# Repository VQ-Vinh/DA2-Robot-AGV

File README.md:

<div align="center">

# 🤖 DA2 · Robot AGV kho hàng kiểu Kiva

**Xe tự hành chui gầm, nâng kệ hàng, chở tới trạm lấy hàng rồi trả về ô và tự đi sạc.**

ROS 2 Jazzy · Nav2 · Gazebo Harmonic · Raspberry Pi 5 · STM32F4 · FreeRTOS · KiCad · FreeCAD

[Mô phỏng & ROS 2](RasPi/README.md) · [Nhật ký quá trình](REPORT.md) · [Firmware STM32](STM32/) · [Mô hình cơ khí](CAD/README.md) · [Mạch PCB](PCB/)

</div>

---

## ✨ Xe làm được gì

| 📦 Nhận đơn | 🛞 Chui gầm & nâng kệ | 🚚 Chở tới trạm | 🔋 Tự sạc | 🚨 Xử lý sự cố |
|:---:|:---:|:---:|:---:|:---:|
| Hàng đợi, ưu tiên, huỷ đơn trên web | Lidar tìm 4 chân kệ, căn giữa ≤ 1 cm | Nav2 + vùng cấm, footprint đổi theo tải | Pin thấp thì về trạm, sạc đủ mới nhận đơn | Dừng khẩn, đường bị chặn, rơi kệ |

---

## 🗺️ Kho hàng

```mermaid
flowchart LR
    subgraph W["Tây kho"]
        IN(["🔵 Khu nhập hàng"])
        CH(["🟢 Trạm sạc"])
        PK(["🟠 Trạm lấy hàng"])
    end
    subgraph N["Dãy bắc · xe vào hướng +y"]
        N1[N1] --- N2[N2] --- N3[N3] --- N4[N4] --- N5[N5]
    end
    AISLE{{"Lối giữa rộng 2.45 m"}}
    subgraph S["Dãy nam · xe vào hướng −y"]
        S1[S1] --- S2[S2] --- S3[S3] --- S4[S4] --- S5[S5]
    end
    W <--> AISLE
    AISLE <--> N
    AISLE <--> S
```

8 kệ 0.75 × 0.75 m nằm trong 10 ô, cách nhau 1.1 m. Bố trí lấy từ một file duy nhất, [`shelves.yaml`](RasPi/src/agv_mission/config/shelves.yaml), từ đó sinh ra world Gazebo, danh sách dock của Nav2 và mặt nạ vùng cấm.

---

## 🧩 Kiến trúc

```mermaid
flowchart TB
    subgraph USER["👤 Người vận hành"]
        WEB["🌐 Web dashboard<br/>điện thoại / laptop"]
    end

    subgraph PI["🍓 Raspberry Pi 5 · ROS 2 Jazzy"]
        DASH["web_dashboard<br/>REST + SSE"]
        OM["order_manager<br/>hàng đợi · SQLite · sự cố"]
        NAV["Nav2<br/>planner · RPP · docking · behaviors"]
        LOC["AMCL + EKF<br/>imu_bias"]
        PM["payload_manager<br/>lọc scan · footprint"]
        SD["shelf_detector<br/>tìm 4 chân kệ"]
    end

    subgraph MCU["⚙️ STM32F407 · FreeRTOS"]
        SPD["PID tốc độ + feedforward"]
        ENC["Encoder"]
        DRV["TB6612FNG × 2"]
        LIFTD["A4988<br/>cơ cấu nâng"]
    end

    LIDAR(["📡 YDLidar"])
    IMU(["🧭 BNO055"])
    BAT(["🔋 INA219"])
    MOT(["4 × GA25-370"])

    WEB <-->|HTTP| DASH
    DASH <--> OM
    OM -->|goal, dock| NAV
    NAV -->|cmd_vel| MCU
    LIDAR --> PM --> NAV
    LIDAR --> SD --> NAV
    LOC --> NAV
    MCU -->|odom, IMU, pin| LOC
    IMU --> MCU
    BAT --> MCU
    SPD --> DRV --> MOT
    LIFTD --> LIFT(["⏫ Động cơ bước nâng kệ"])
    MOT --> ENC --> SPD
```

---

## 🔁 Một đơn hàng

```mermaid
sequenceDiagram
    autonumber
    actor U as 👤 Người vận hành
    participant OM as order_manager
    participant N as Nav2 / docking
    participant L as Cơ cấu nâng

    U->>OM: add ke_03 tram_lay_hang
    OM->>N: tới staging trước ô (đoạn cuối thẳng)
    OM->>N: chui gầm theo chân kệ (lidar)
    OM->>OM: kiểm tra hướng ≤ 8°
    OM->>L: nâng
    OM->>N: lùi ra · chở tới trạm
    OM-->>U: đã tới, chờ lấy hàng
    U->>OM: confirm
    OM->>N: về ô · vào ô theo bản đồ
    OM->>OM: kiểm tra hướng ≤ 8°, vị trí ≤ 10 cm
    OM->>L: hạ
    OM->>N: lùi ra · về trạm sạc
```

---

## 🚨 Khi có sự cố

```mermaid
flowchart LR
    E{"Sự cố"} -->|Dừng khẩn<br/>Đường bị chặn > 60 s| R["⏸️ Xe dừng<br/>chờ người"]
    E -->|Rơi kệ<br/>Cơ cấu nâng lỗi| F["⛔ Đơn lỗi<br/>kệ chưa rõ vị trí"]
    E -->|Lỗi trước khi nâng kệ| Q["↩️ Trả đơn về hàng đợi"]
    R -->|"Đã xử lý"| C["▶️ Làm lại đúng bước đang dở"]
    F -->|"shelf ke_xx Ny"| C2["📍 Cập nhật vị trí kệ"]
```

```mermaid
flowchart LR
    B["🔋 Pin < 30 % + 10 % dự trữ cho đơn"] --> G["Về trạm sạc"] --> H["Sạc tới 80 %"] --> J["Nhận đơn tiếp"]
```

---

## 🧭 Định vị

```mermaid
flowchart LR
    ENC["Encoder bánh"] --> WO["/wheel/odom<br/>vx tin được · wz kém"]
    GYRO["Gyro"] --> RAW["/imu/raw"] --> IB["imu_bias<br/>học bias khi bánh đứng yên"] --> IMU["/imu"]
    WO --> EKF["EKF"]
    IMU --> EKF
    EKF --> ODOM["/odom"]
    ODOM --> AMCL["AMCL + bản đồ"]
    SCAN["Lidar"] --> AMCL
    AMCL --> MAP["vị trí trên bản đồ"]
```

---

## 📊 Kết quả trong mô phỏng

8 đơn liên tiếp, có mô phỏng vùng chết động cơ giống firmware (≥ 100 RPM):

| | Trước khi chỉnh | Sau khi chỉnh |
|---|:---:|:---:|
| Đơn xong | 8/8 | **8/8** |
| Thời gian TB / đơn | 105 s | **88 s** |
| Quay thừa khi trả kệ (lớn nhất) | 4198° | **75°** |
| Nav2 phải tự hồi phục | nhiều lần | **0** |
| Góc trôi khi đứng yên 5 phút | 2.4°–12° | **0.05°** |

| Bài thử | Kết quả |
|---|---|
| Chui gầm theo chân kệ (kệ đặt lệch) | 6/6, lệch ngang ≤ 0.9 cm · theo bản đồ chỉ 2/6 |
| Đơn hàng + ưu tiên + huỷ | 3/3 |
| Sạc giữa chừng | 3/3 đơn, tự về sạc rồi làm tiếp |
| Sự cố (dừng khẩn, rơi kệ, tường chắn) | dừng khẩn & rơi kệ: 4/4 lần · tường chắn: 2/4 lần |

Cách đo, các lần sai và cách sửa: [REPORT.md](REPORT.md).

---

## 🛣️ Tiến độ

```mermaid
timeline
    title Các mốc chính
    09/2026 : Firmware STM32 · PID tốc độ
            : Chọn ROS 2 Jazzy + Gazebo Harmonic
    10/2026 : Mô phỏng · EKF · SLAM · Nav2
            : Web dashboard
            : Kiva 1 · nâng kệ · Kiva 2 · tìm chân kệ
            : Kiva 3 · đơn hàng · Kiva 4 · pin & sạc · Kiva 5 · sự cố
            : Mô hình cơ khí FreeCAD
            : PCB · chốt linh kiện · sơ đồ chân CubeMX · sơ đồ nguyên lý · xếp linh kiện nháp
            : PCB 2 lớp · đi dây · DRC sạch · Gerber JLCPCB
            : CAD · PCB thật · công tắc hành trình
    Tiếp theo : Đặt mạch · ướm footprint với module thật · mua linh kiện
              : Firmware 4 bánh + cơ cấu nâng · cầu nối UART Pi ↔ STM32
              : Lắp và chạy trên xe thật
```

---

## 🚀 Chạy thử

```bash
# WSL Ubuntu 24.04 + ROS 2 Jazzy (xem RasPi/README.md để cài)
cd ~/agv_ws && colcon build --symlink-install && source install/setup.bash
ros2 launch agv_gazebo sim.launch.py nav:=true
```

Sau đó mở **http://localhost:8080**, chọn kệ và trạm rồi bấm **Tạo đơn**.

---

## 📁 Cấu trúc repo

```mermaid
flowchart LR
    R["📂 Src"] --> RP["📂 RasPi/src<br/>ROS 2"]
    R --> ST["📂 STM32<br/>firmware"]
    R --> RE["📄 REPORT.md<br/>nhật ký"]
    R --> CA["📂 CAD<br/>mô hình FreeCAD"]
    R --> PC["📂 PCB<br/>board mẹ KiCad"]
    RP --> D["agv_description<br/>URDF"]
    RP --> G["agv_gazebo<br/>world · sim · bài thử"]
    RP --> L["agv_localization<br/>EKF · imu_bias"]
    RP --> NV["agv_navigation<br/>SLAM · Nav2 · docking"]
    RP --> M["agv_mission<br/>đơn hàng · dashboard"]
    ST --> APP["App<br/>logic"]
    ST --> MOD["Modules<br/>driver"]
    ST --> CORE["Core<br/>CubeMX sinh"]
```

<div align="center">

Đồ án 2 · HK261

</div>

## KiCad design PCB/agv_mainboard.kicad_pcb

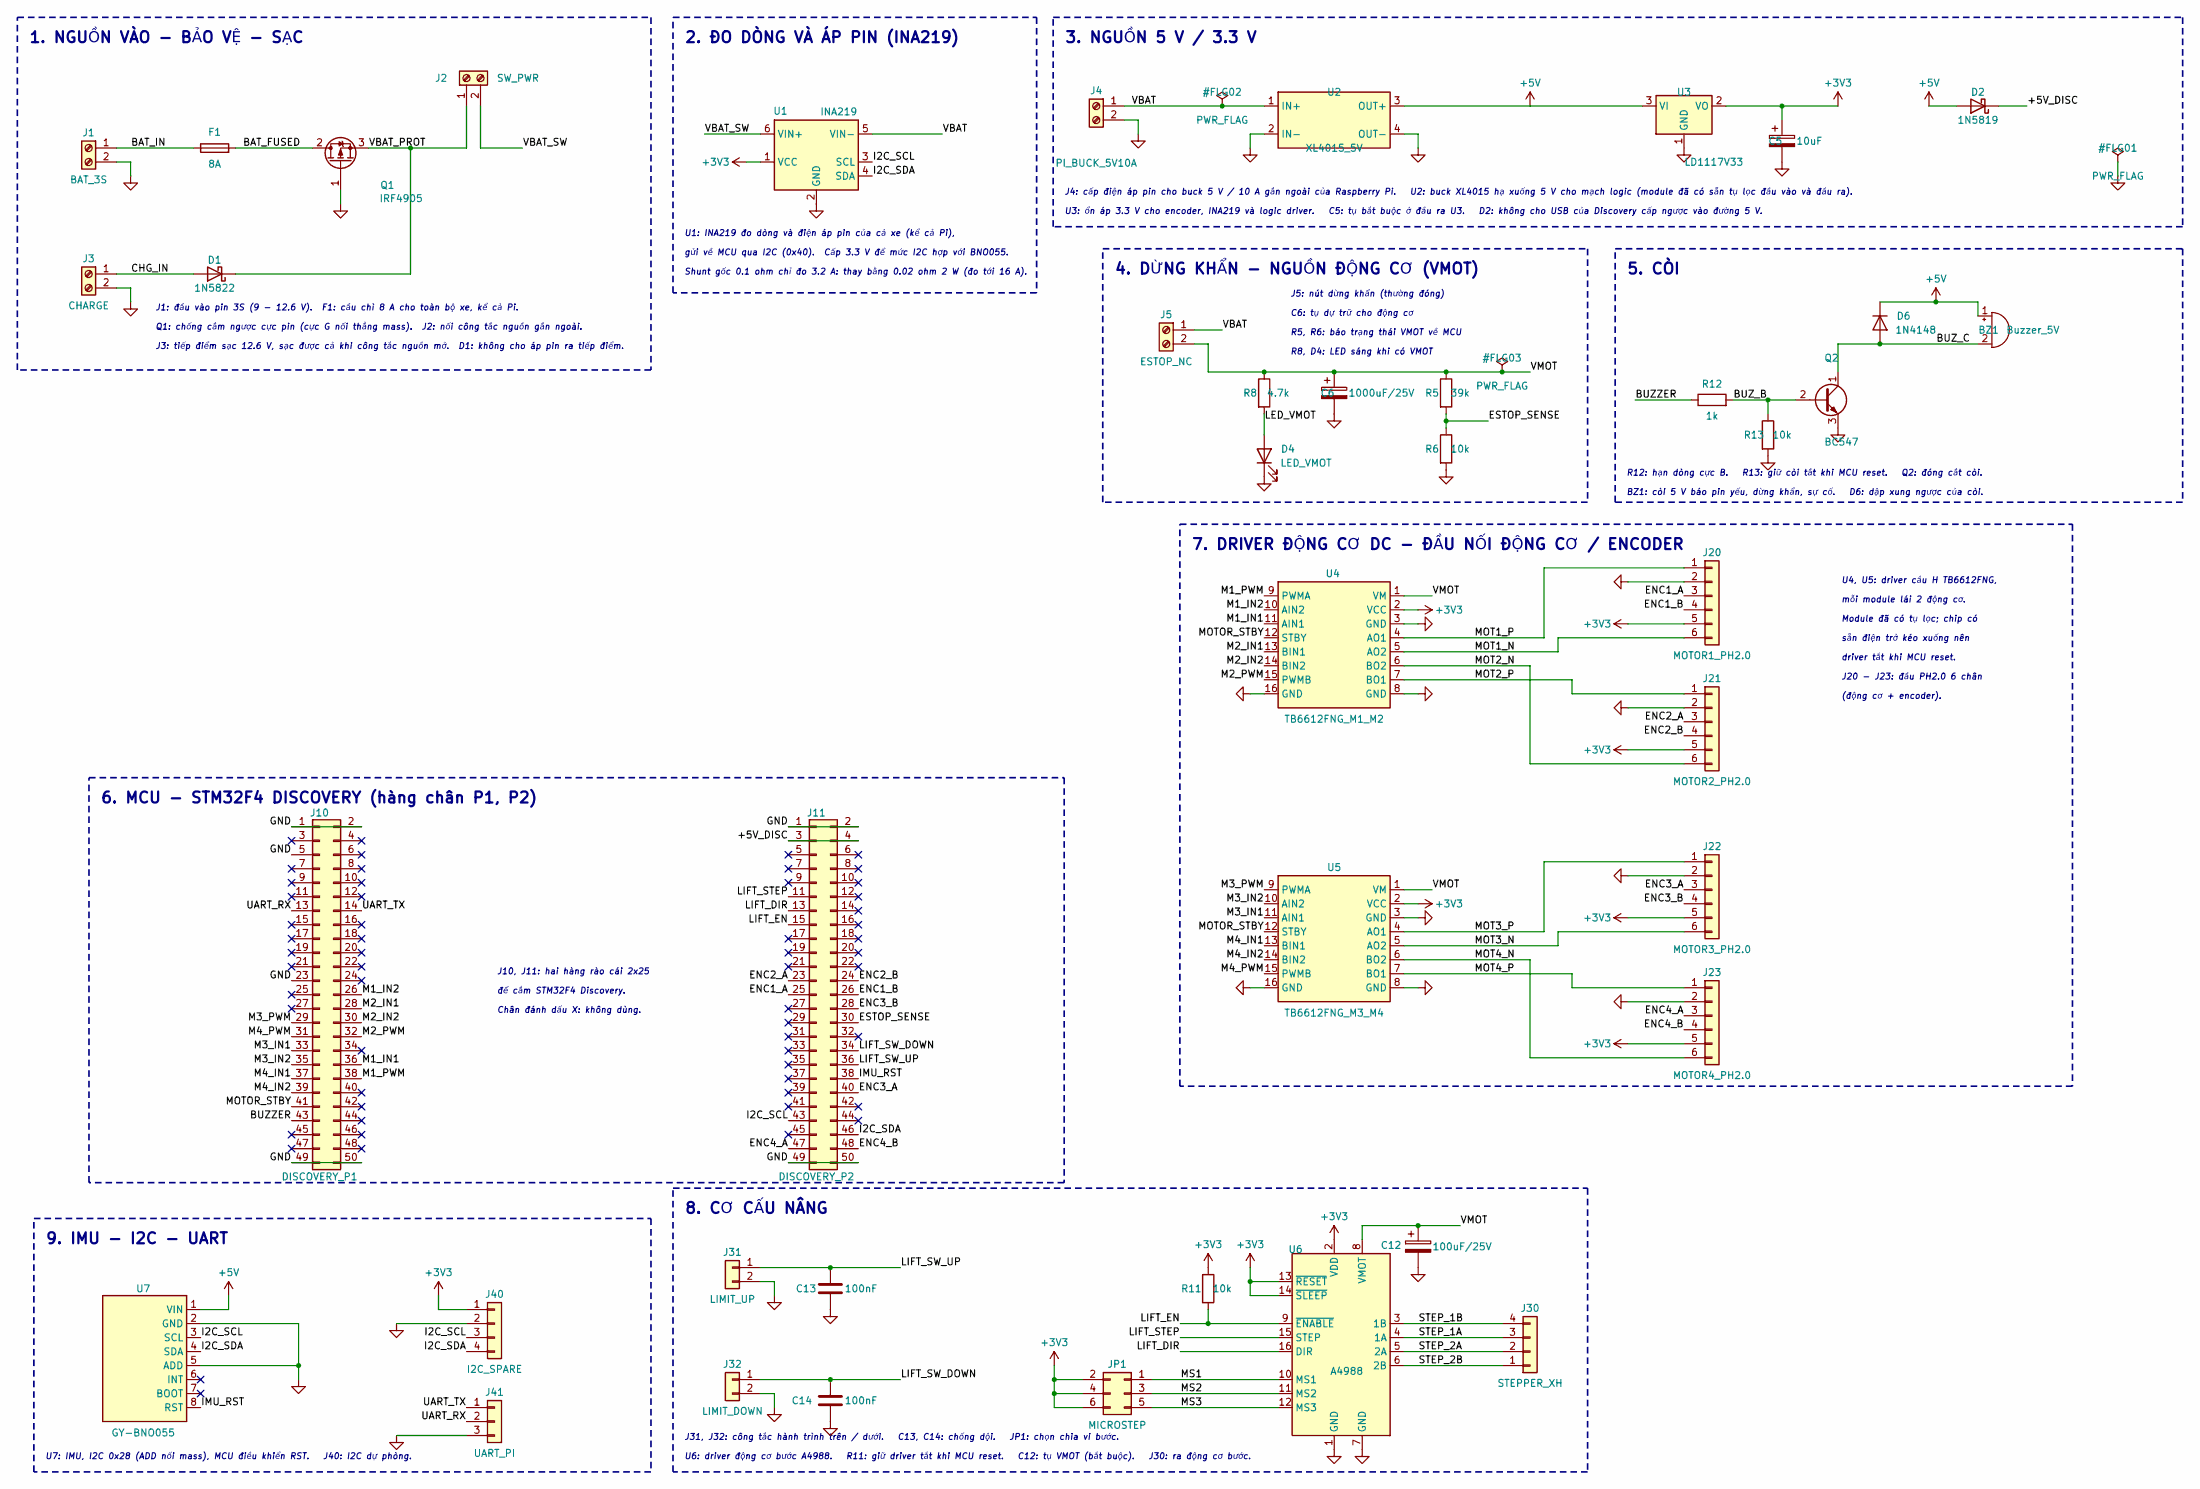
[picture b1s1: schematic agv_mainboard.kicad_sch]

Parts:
BZ1: Buzzer_5V; Buzzer_12x9.5RM7.6
C5: 10uF; CP_Radial_D5.0mm_P2.00mm
C6: 1000uF/25V; CP_Radial_D10.0mm_P5.00mm
C12: 100uF/25V; CP_Radial_D6.3mm_P2.50mm
C13, C14: 100nF; C_Disc_D5.0mm_W2.5mm_P5.00mm
D1: 1N5822; D_DO-201AD_P15.24mm_Horizontal
D2: 1N5819; D_DO-41_SOD81_P10.16mm_Horizontal
D4: LED_VMOT; LED_D3.0mm
D6: 1N4148; D_DO-35_SOD27_P7.62mm_Horizontal
F1: 8A; Fuseholder_Cylinder-5x20mm_Schurter_0031_8201_Horizontal_Op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
J1: BAT_3S; TerminalBlock_MaiXu_MX126-5.0-02P_1x02_P5.00mm
J2: SW_PWR; TerminalBlock_MaiXu_MX126-5.0-02P_1x02_P5.00mm
J3: CHARGE; TerminalBlock_MaiXu_MX126-5.0-02P_1x02_P5.00mm
J4: PI_BUCK_5V10A; TerminalBlock_MaiXu_MX126-5.0-02P_1x02_P5.00mm
J5: ESTOP_NC; TerminalBlock_MaiXu_MX126-5.0-02P_1x02_P5.00mm
J10: DISCOVERY_P1; PinHeader_2x25_P2.54mm_Vertical
J11: DISCOVERY_P2; PinHeader_2x25_P2.54mm_Vertical
J20: MOTOR1_PH2.0; JST_PH_S6B-PH-K_1x06_P2.00mm_Horizontal
J21: MOTOR2_PH2.0; JST_PH_S6B-PH-K_1x06_P2.00mm_Horizontal
J22: MOTOR3_PH2.0; JST_PH_S6B-PH-K_1x06_P2.00mm_Horizontal
J23: MOTOR4_PH2.0; JST_PH_S6B-PH-K_1x06_P2.00mm_Horizontal
J30: STEPPER_XH; JST_XH_B4B-XH-A_1x04_P2.50mm_Vertical
J31: LIMIT_UP; JST_XH_B2B-XH-A_1x02_P2.50mm_Vertical
J32: LIMIT_DOWN; JST_XH_B2B-XH-A_1x02_P2.50mm_Vertical
J40: I2C_SPARE; JST_XH_B4B-XH-A_1x04_P2.50mm_Vertical
J41: UART_PI; JST_XH_B3B-XH-A_1x03_P2.50mm_Vertical
JP1: MICROSTEP; PinHeader_2x03_P2.54mm_Vertical
Q1: IRF4905; TO-220-3_Vertical
Q2: BC547; TO-92_Inline_Wide
R5: 39k; R_Axial_DIN0207_L6.3mm_D2.5mm_P10.16mm_Horizontal
R6, R11, R13: 10k; R_Axial_DIN0207_L6.3mm_D2.5mm_P10.16mm_Horizontal
R8: 4.7k; R_Axial_DIN0207_L6.3mm_D2.5mm_P10.16mm_Horizontal
R12: 1k; R_Axial_DIN0207_L6.3mm_D2.5mm_P10.16mm_Horizontal
U1: INA219; INA219_Module
U2: XL4015_5V; XL4015_Module
U3: LD1117V33; TO-220-3_Vertical
U4: TB6612FNG_M1_M2; TB6612FNG_Module
U5: TB6612FNG_M3_M4; TB6612FNG_Module
U6: A4988; Pololu_Breakout-16_15.2x20.3mm
U7: GY-BNO055; PinSocket_1x08_P2.54mm_Vertical

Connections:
+3V3: C5.1, J20.5, J21.5, J22.5, J23.5, J40.1, JP1.2, JP1.4, JP1.6, R11.1, U1.1 (VCC), U3.2 (VO), U4.2 (VCC), U5.2 (VCC), U6.2 (VDD), U6.13 (~RESET), U6.14 (~SLEEP)
+5V: BZ1.1 (+), D2.2 (A), D6.1 (K), U2.3 (OUT+), U3.3 (VI), U7.1 (VIN)
/+5V_DISC: D2.1 (K), J11.3, J11.4
/BAT_FUSED: F1.2, Q1.2 (D)
/BAT_IN: F1.1, J1.1
/BUZZER: J10.43, R12.1
/BUZ_B: Q2.2 (B), R12.2, R13.1
/BUZ_C: BZ1.2 (-), D6.2 (A), Q2.1 (C)
/CHG_IN: D1.2 (A), J3.1
/ENC1_A: J11.25, J20.3
/ENC1_B: J11.26, J20.4
/ENC2_A: J11.23, J21.3
/ENC2_B: J11.24, J21.4
/ENC3_A: J11.40, J22.3
/ENC3_B: J11.28, J22.4
/ENC4_A: J11.47, J23.3
/ENC4_B: J11.48, J23.4
/ESTOP_SENSE: J11.30, R5.2, R6.1
/I2C_SCL: J11.43, J40.3, U1.3 (SCL), U7.3 (SCL)
/I2C_SDA: J11.46, J40.4, U1.4 (SDA), U7.4 (SDA)
/IMU_RST: J11.38, U7.8 (RST)
/LED_VMOT: D4.2 (A), R8.2
/LIFT_DIR: J11.13, U6.16 (DIR)
/LIFT_EN: J11.15, R11.2, U6.9 (~ENABLE)
/LIFT_STEP: J11.11, U6.15 (STEP)
/LIFT_SW_DOWN: C14.1, J11.34, J32.1
/LIFT_SW_UP: C13.1, J11.36, J31.1
/M1_IN1: J10.36, U4.11 (AIN1)
/M1_IN2: J10.26, U4.10 (AIN2)
/M1_PWM: J10.38, U4.9 (PWMA)
/M2_IN1: J10.28, U4.13 (BIN1)
/M2_IN2: J10.30, U4.14 (BIN2)
/M2_PWM: J10.32, U4.15 (PWMB)
/M3_IN1: J10.33, U5.11 (AIN1)
/M3_IN2: J10.35, U5.10 (AIN2)
/M3_PWM: J10.29, U5.9 (PWMA)
/M4_IN1: J10.37, U5.13 (BIN1)
/M4_IN2: J10.39, U5.14 (BIN2)
/M4_PWM: J10.31, U5.15 (PWMB)
/MOT1_N: J20.6, U4.5 (AO2)
/MOT1_P: J20.1, U4.4 (AO1)
/MOT2_N: J21.6, U4.6 (BO2)
/MOT2_P: J21.1, U4.7 (BO1)
/MOT3_N: J22.6, U5.5 (AO2)
/MOT3_P: J22.1, U5.4 (AO1)
/MOT4_N: J23.6, U5.6 (BO2)
/MOT4_P: J23.1, U5.7 (BO1)
/MOTOR_STBY: J10.41, U4.12 (STBY), U5.12 (STBY)
/MS1: JP1.1, U6.10 (MS1)
/MS2: JP1.3, U6.11 (MS2)
/MS3: JP1.5, U6.12 (MS3)
/STEP_1A: J30.3, U6.4 (1A)
/STEP_1B: J30.4, U6.3 (1B)
/STEP_2A: J30.2, U6.5 (2A)
/STEP_2B: J30.1, U6.6 (2B)
/UART_RX: J10.13, J41.2
/UART_TX: J10.14, J41.1
/VBAT: J4.1, J5.1, U1.5 (VIN-), U2.1 (IN+)
/VBAT_PROT: D1.1 (K), J2.1, Q1.3 (S)
/VBAT_SW: J2.2, U1.6 (VIN+)
/VMOT: C6.1, C12.1, J5.2, R5.1, R8.1, U4.1 (VM), U5.1 (VM), U6.8 (VMOT)
GND: C5.2, C6.2, C12.2, C13.2, C14.2, D4.1 (K), J1.2, J3.2, J4.2, J10.1, J10.2, J10.5, J10.23, J10.49, J10.50, J11.1, J11.2, J11.49, J11.50, J20.2, J21.2, J22.2, J23.2, J31.2, J32.2, J40.2, J41.3, Q1.1 (G), Q2.3 (E), R6.2, R13.2, U1.2 (GND), U2.2 (IN-), U2.4 (OUT-), U3.1 (GND), U4.3 (GND), U4.8 (GND), U4.16 (GND), U5.3 (GND), U5.8 (GND), U5.16 (GND), U6.1 (GND), U6.7 (GND), U7.2 (GND), U7.5 (ADD)

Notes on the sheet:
driver tắt khi MCU reset.
để cắm STM32F4 Discovery.
R5, R6: báo trạng thái VMOT về MCU
3. NGUỒN 5 V / 3.3 V
J5: nút dừng khẩn (thường đóng)
1. NGUỒN VÀO - BẢO VỆ - SẠC
U3: ổn áp 3.3 V cho encoder, INA219 và logic driver. C5: tụ bắt buộc ở đầu ra U3. D2: không cho USB của Discovery cấp ngược vào đường 5 V.
gửi về MCU qua I2C (0x40). Cấp 3.3 V để mức I2C hợp với BNO055.
J20 - J23: đầu PH2.0 6 chân
sẵn điện trở kéo xuống nên
5. CÒI
2. ĐO DÒNG VÀ ÁP PIN (INA219)
9. IMU - I2C - UART
BZ1: còi 5 V báo pin yếu, dừng khẩn, sự cố. D6: dập xung ngược của còi.
J4: cấp điện áp pin cho buck 5 V / 10 A gắn ngoài của Raspberry Pi. U2: buck XL4015 hạ xuống 5 V cho mạch logic (module đã có sẵn tụ lọc đầu vào và đầu ra).
U4, U5: driver cầu H TB6612FNG,
7. DRIVER ĐỘNG CƠ DC - ĐẦU NỐI ĐỘNG CƠ / ENCODER
J10, J11: hai hàng rào cái 2x25
J3: tiếp điểm sạc 12.6 V, sạc được cả khi công tắc nguồn mở. D1: không cho áp pin ra tiếp điểm.
J1: đầu vào pin 3S (9 - 12.6 V). F1: cầu chì 8 A cho toàn bộ xe, kể cả Pi.
Module đã có tụ lọc; chip có
Q1: chống cắm ngược cực pin (cực G nối thẳng mass). J2: nối công tắc nguồn gắn ngoài.
R8, D4: LED sáng khi có VMOT
Shunt gốc 0.1 ohm chỉ đo 3.2 A: thay bằng 0.02 ohm 2 W (đo tới 16 A).
(động cơ + encoder).
J31, J32: công tắc hành trình trên / dưới. C13, C14: chống dội. JP1: chọn chia vi bước.
6. MCU - STM32F4 DISCOVERY (hàng chân P1, P2)
C6: tụ dự trữ cho động cơ
Chân đánh dấu X: không dùng.
4. DỪNG KHẨN - NGUỒN ĐỘNG CƠ (VMOT)
U1: INA219 đo dòng và điện áp pin của cả xe (kể cả Pi),
8. CƠ CẤU NÂNG
U7: IMU, I2C 0x28 (ADD nối mass), MCU điều khiển RST. J40: I2C dự phòng.
mỗi module lái 2 động cơ.
U6: driver động cơ bước A4988. R11: giữ driver tắt khi MCU reset. C12: tụ VMOT (bắt buộc). J30: ra động cơ bước.
R12: hạn dòng cực B. R13: giữ còi tắt khi MCU reset. Q2: đóng cắt còi.

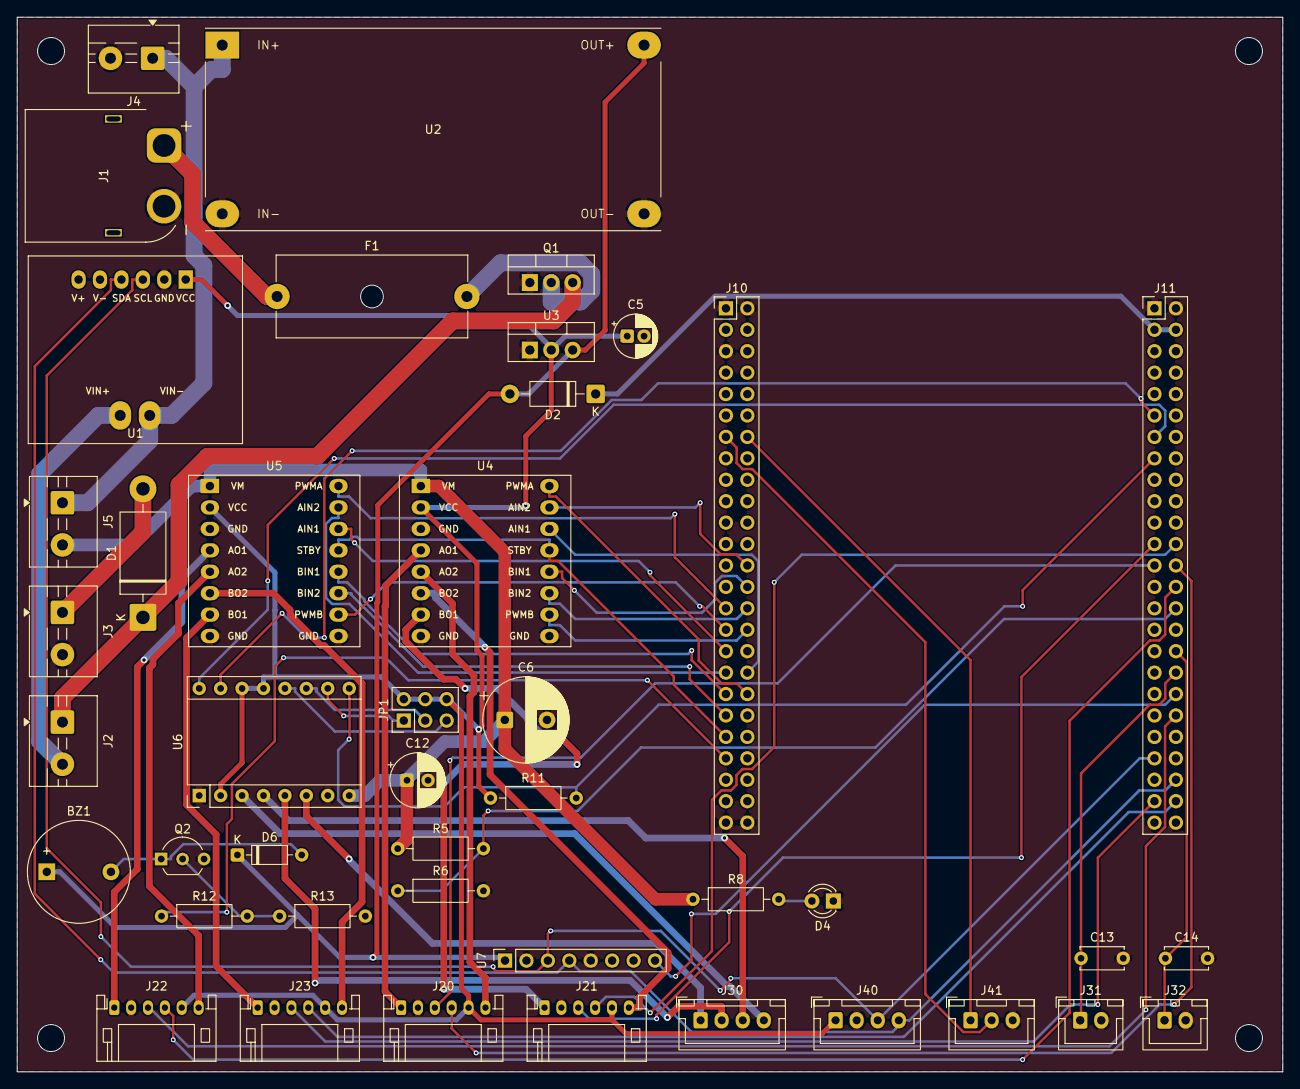
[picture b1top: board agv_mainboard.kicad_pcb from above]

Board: 2 copper layers, 150.0 x 125.0 mm, 47 parts (0 on the bottom side), 62 nets.

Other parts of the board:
H1, H2, H3, H4: MountingHole_3.2mm_M3

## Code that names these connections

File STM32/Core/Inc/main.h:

/* USER CODE BEGIN Header */
/**
  ******************************************************************************
  * @file           : main.h
  * @brief          : Header for main.c file.
  *                   This file contains the common defines of the application.
  ******************************************************************************
  * @attention
  *
  * Copyright (c) 2026 STMicroelectronics.
  * All rights reserved.
  *
  * This software is licensed under terms that can be found in the LICENSE file
  * in the root directory of this software component.
  * If no LICENSE file comes with this software, it is provided AS-IS.
  *
  ******************************************************************************
  */
/* USER CODE END Header */

/* Define to prevent recursive inclusion -------------------------------------*/
#ifndef __MAIN_H
#define __MAIN_H

#ifdef __cplusplus
extern "C" {
#endif

/* Includes ------------------------------------------------------------------*/
#include "stm32f4xx_hal.h"

/* Private includes ----------------------------------------------------------*/
/* USER CODE BEGIN Includes */

/* USER CODE END Includes */

/* Exported types ------------------------------------------------------------*/
/* USER CODE BEGIN ET */

/* USER CODE END ET */

/* Exported constants --------------------------------------------------------*/
/* USER CODE BEGIN EC */

/* USER CODE END EC */

/* Exported macro ------------------------------------------------------------*/
/* USER CODE BEGIN EM */

/* USER CODE END EM */

/* Exported functions prototypes ---------------------------------------------*/
void Error_Handler(void);

/* USER CODE BEGIN EFP */

/* USER CODE END EFP */

/* Private defines -----------------------------------------------------------*/
#define LIFT_EN_Pin GPIO_PIN_2
#define LIFT_EN_GPIO_Port GPIOE
#define LIFT_DIR_Pin GPIO_PIN_4
#define LIFT_DIR_GPIO_Port GPIOE
#define M1_IN2_Pin GPIO_PIN_8
#define M1_IN2_GPIO_Port GPIOE
#define M2_IN1_Pin GPIO_PIN_10
#define M2_IN1_GPIO_Port GPIOE
#define M2_IN2_Pin GPIO_PIN_12
#define M2_IN2_GPIO_Port GPIOE
#define M3_IN1_Pin GPIO_PIN_15
#define M3_IN1_GPIO_Port GPIOE
#define M3_IN2_Pin GPIO_PIN_11
#define M3_IN2_GPIO_Port GPIOB
#define M1_IN1_Pin GPIO_PIN_12
#define M1_IN1_GPIO_Port GPIOB
#define M4_IN1_Pin GPIO_PIN_13
#define M4_IN1_GPIO_Port GPIOB
#define M4_IN2_Pin GPIO_PIN_15
#define M4_IN2_GPIO_Port GPIOB
#define MOTOR_STBY_Pin GPIO_PIN_9
#define MOTOR_STBY_GPIO_Port GPIOD
#define BUZZER_Pin GPIO_PIN_11
#define BUZZER_GPIO_Port GPIOD
#define IMU_RST_Pin GPIO_PIN_11
#define IMU_RST_GPIO_Port GPIOC
#define LIFT_SW_UP_Pin GPIO_PIN_0
#define LIFT_SW_UP_GPIO_Port GPIOD
#define LIFT_SW_DOWN_Pin GPIO_PIN_2
#define LIFT_SW_DOWN_GPIO_Port GPIOD
#define AUDIO_RST_Pin GPIO_PIN_4
#define AUDIO_RST_GPIO_Port GPIOD
#define ESTOP_SENSE_Pin GPIO_PIN_6
#define ESTOP_SENSE_GPIO_Port GPIOD

/* USER CODE BEGIN Private defines */

/* USER CODE END Private defines */

#ifdef __cplusplus
}
#endif

#endif /* __MAIN_H */
